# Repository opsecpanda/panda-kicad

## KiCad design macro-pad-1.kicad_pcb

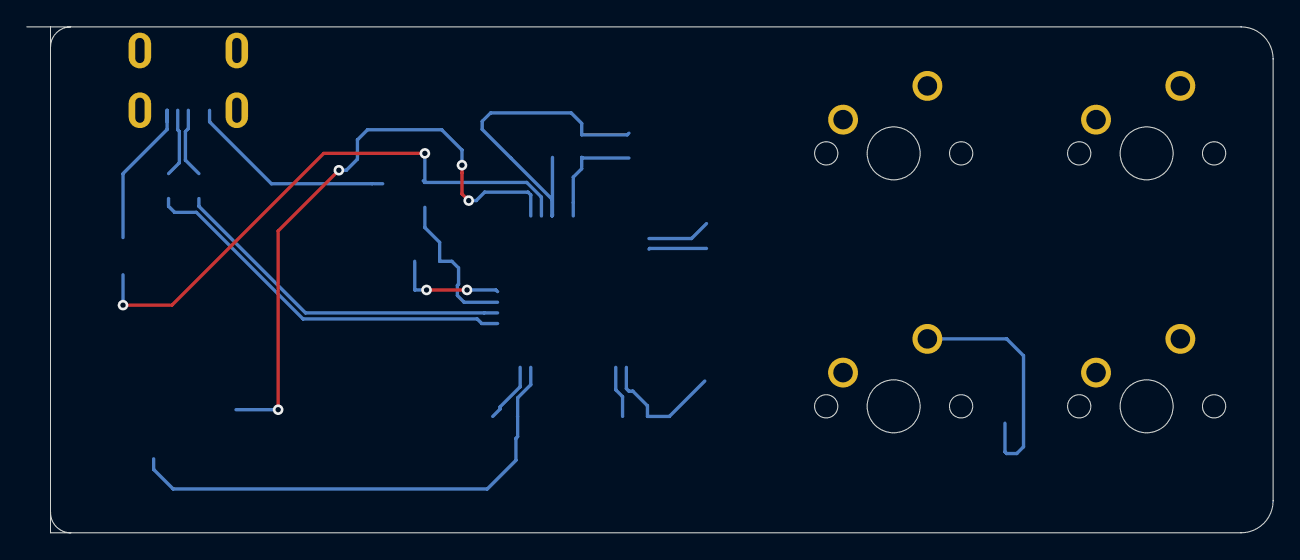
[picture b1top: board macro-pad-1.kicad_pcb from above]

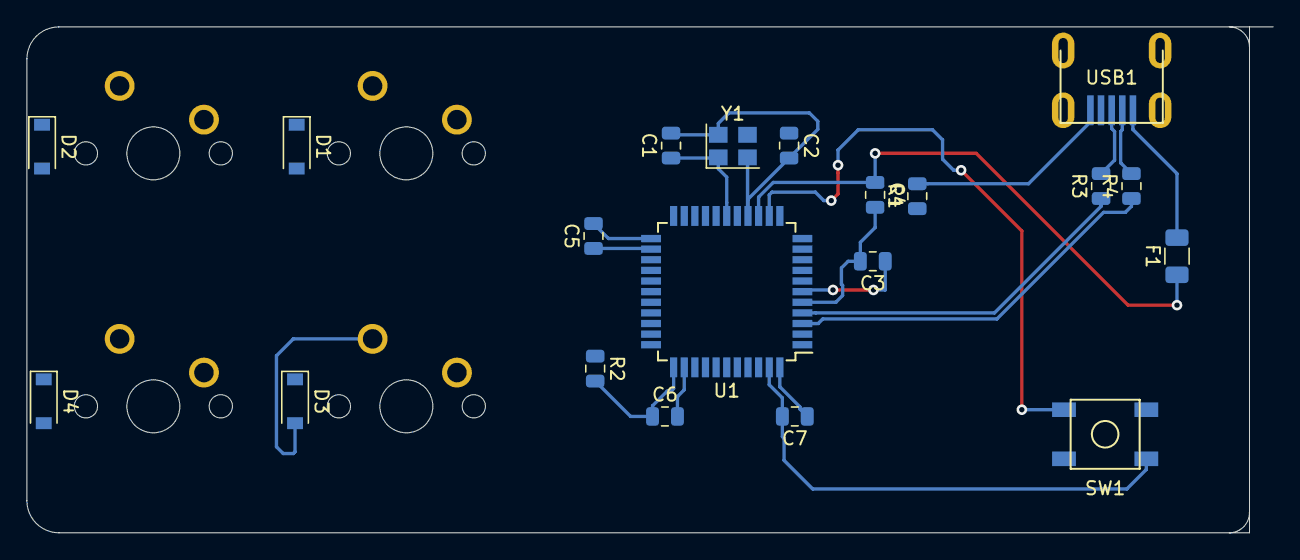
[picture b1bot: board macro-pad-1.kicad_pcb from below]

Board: 2 copper layers, 93.9 x 38.1 mm, 24 parts (20 on the bottom side), 20 nets.

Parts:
C1, C2: 22pF; C_0805_2012Metric
C3: 1uF; C_0805_2012Metric
C4, C5, C6: 0.1uF; C_0805_2012Metric
C7: 10uF; C_0805_2012Metric
D1, D2, D3, D4: D_Small; D_SOD-123
F1: 500mA; Fuse_1206_3216Metric
MX1, MX2, MX3, MX4: MX-NoLED; MXOnly-1U-NoLED
R1, R2: 10k; R_0805_2012Metric
R3, R4: 22; R_0805_2012Metric
SW1: SW_Push; SKQG-1155865
U1: ATmega32U4-AU; TQFP-44_10x10mm_P0.8mm
USB1: Molex-0548190589
Y1: Crystal_GND24_Small; Crystal_SMD_3225-4Pin_3.2x2.5mm

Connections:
+5V: C4.1, C5.1, C6.1, C7.1, F1.1, R2.2, U1.2, U1.7, U1.14, U1.24, U1.34, U1.44
COL0: MX1.1, MX3.1, U1.29
COL1: MX2.1, MX4.1, U1.28
D+: R3.2, USB1.3
D-: R4.2, USB1.4
GND: C1.2, C2.2, C3.2, C4.2, C5.2, C6.2, C7.2, R1.2, SW1.1, U1.5, U1.15, U1.23, U1.35, U1.43, USB1.1, Y1.2, Y1.4
unnamed: C1.1, U1.17, Y1.1
unnamed: C2.1, U1.16, Y1.3
unnamed: C3.1, U1.6
unnamed: D1.2, MX1.2
unnamed: D2.2, MX2.2
unnamed: D3.2, MX3.2
unnamed: D4.2, MX4.2
unnamed: R1.1, U1.33
unnamed: R2.1, SW1.2, U1.13
unnamed: R3.1, U1.4
unnamed: R4.1, U1.3
ROW0: D1.1, D2.1, U1.27
ROW1: D3.1, D4.1, U1.30
VCC: F1.2, USB1.5

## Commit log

2020-12-01 Initialize project
    just starting up
2020-12-01 Add submodules
2020-12-01 Adding footprint libs
2020-12-02 Schematic done maybe
2020-12-03 PCB changes, not done
2020-12-03 PCB routing, not done
